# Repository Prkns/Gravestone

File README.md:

💀

6 Key Macropad with USB-C... Still a work in progress.

Feel free to contribute to this project 👍

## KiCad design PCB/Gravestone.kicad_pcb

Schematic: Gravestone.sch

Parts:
C1, C2: 22pF; C_0805_2012Metric_Pad1.15x1.40mm_HandSolder
C3, C4, C5: 0.1uF; C_0805_2012Metric_Pad1.15x1.40mm_HandSolder
C6: 10uF; C_0805_2012Metric_Pad1.15x1.40mm_HandSolder
C7: 1uF; C_0805_2012Metric_Pad1.15x1.40mm_HandSolder
D1: PRTR5V0U2X; SOT-23-6
D2, D3, D4, D5, D6, D7: D_Small; D_SOD-123
F1: 500mA; Fuse_1206_3216Metric
J1: USB_C_Receptacle_USB2.0; USB_C_Receptacle_HRO_TYPE-C-31-M-12
MX1, MX2, MX3, MX4, MX5, MX6: MX-NoLED; MXOnly-1U-NoLED
R1, R7: 10k; R_0805
R2, R3: 5.1k; R_0805
R4, R5: 22; R_0805
SW1: SW_PUSH; SW_SPST_TL3342
U1: ATmega32U2-AU; ATMEGA32U2-AU
Y1: 16MHz; Crystal_SMD_3225-4pin_3.2x2.5mm

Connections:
+5V: C3.1, C4.1, C5.1, C6.1, F1.1, R1.2, U1.4 (VCC), U1.31 (UVCC), U1.32 (AVCC)
COL0: MX1.1, MX4.1, U1.6 (PD0)
COL1: MX2.1, MX5.1, U1.7 (PD1)
COL2: MX3.1, MX6.1, U1.8 (PD2)
D+: D1.6 (IO4), J1.A6, J1.B6, R4.2
D-: D1.1 (IO1), J1.A7, J1.B7, R5.2
GND: C1.2, C2.2, C3.2, C4.2, C5.2, C6.2, C7.2, D1.2 (VN), J1.A1B12, J1.B1A12, J1.S1, R2.1, R3.1, R7.2, SW1.1, U1.3 (GND), U1.28 (UGND), Y1.2, Y1.4
unnamed: C1.1, U1.1 (XTAL1), Y1.1
unnamed: C2.1, U1.2 (PC0/XTAL2), Y1.3
unnamed: C7.1, U1.27 (UCAP)
unnamed: D2.1 (K), MX1.2
unnamed: D3.1 (K), MX2.2
unnamed: D4.1 (K), MX3.2
unnamed: D5.1 (K), MX4.2
unnamed: D6.1 (K), MX5.2
unnamed: D7.1 (K), MX6.2
unnamed: J1.A5, R2.2
unnamed: J1.B5, R3.2
unnamed: R1.1, SW1.2, U1.24 (PC1/~RESET)
unnamed: R4.1, U1.29 (D+)
unnamed: R5.1, U1.30 (D-)
unnamed: R7.1, U1.13 (~HWB~/PD7)
ROW0: D2.2 (A), D3.2 (A), D4.2 (A), U1.9 (PD3)
ROW1: D5.2 (A), D6.2 (A), D7.2 (A)
ROW2: U1.10 (PD4)
VBUS: D1.5 (VP), F1.2, J1.A4B9, J1.B4A9

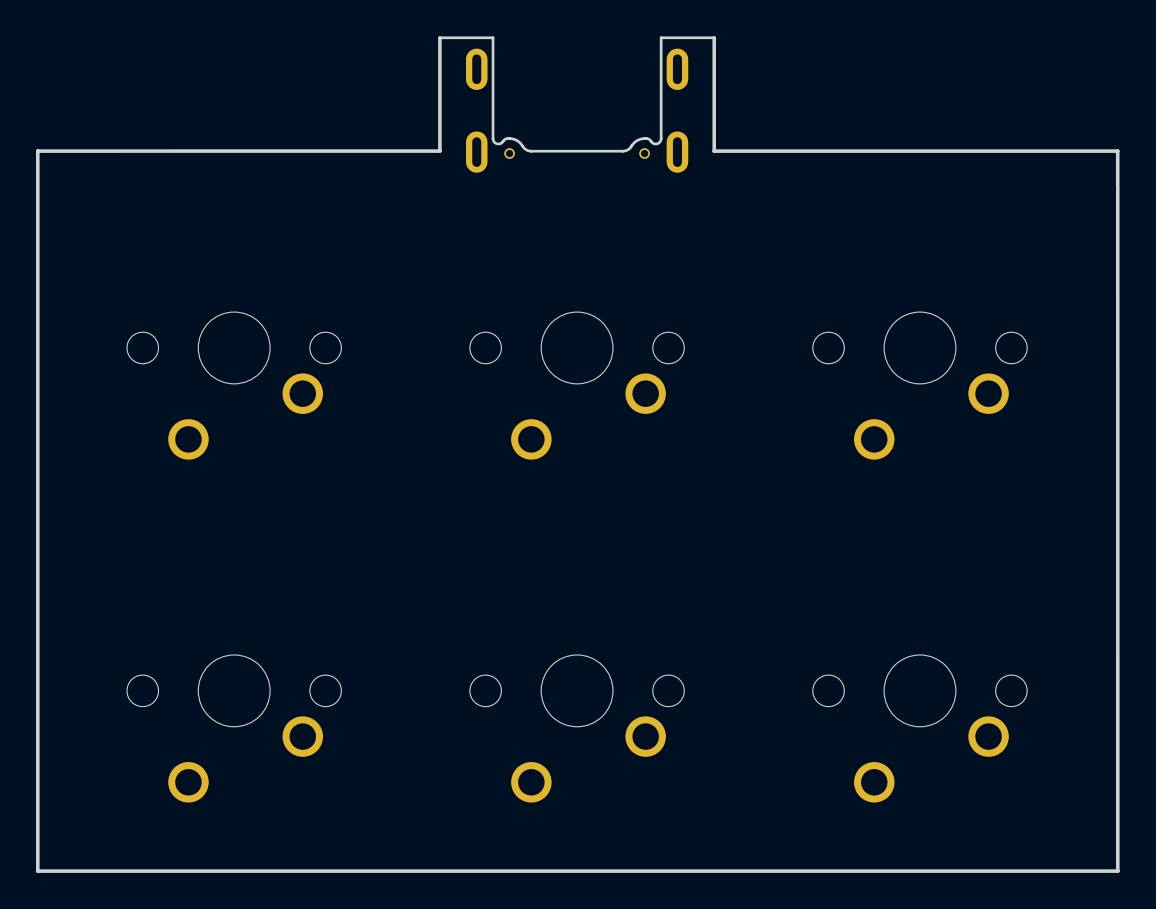
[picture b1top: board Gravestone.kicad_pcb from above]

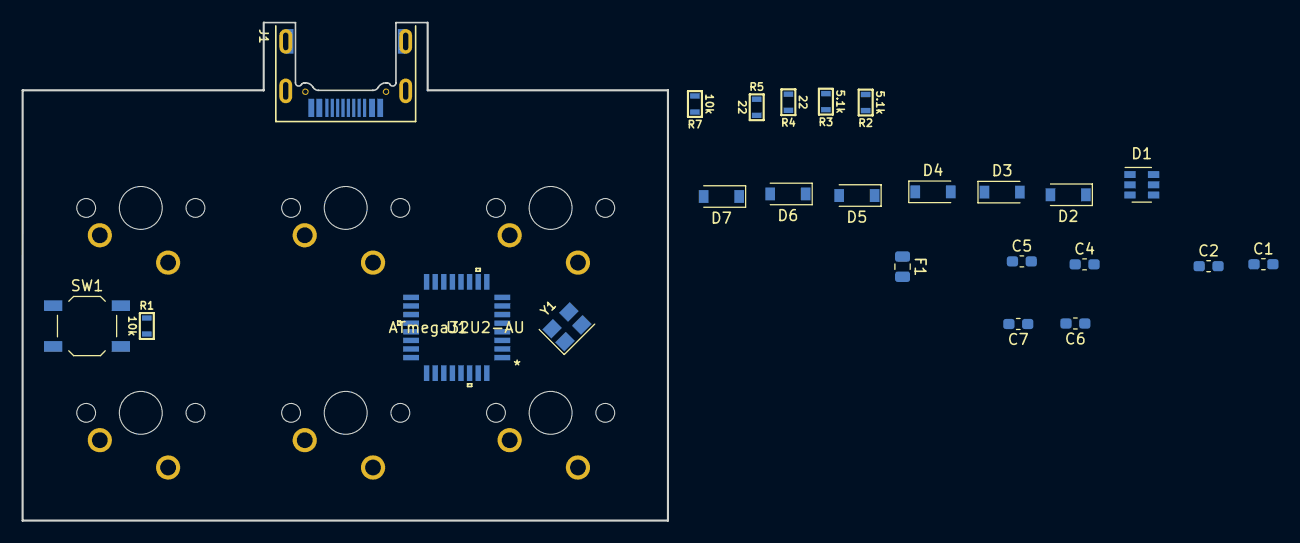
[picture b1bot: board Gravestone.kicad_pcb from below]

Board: 2 copper layers, 60.0 x 46.3 mm, 30 parts (24 on the bottom side), 25 nets, no tracks yet.

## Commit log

2020-08-26 updated ignore
2020-08-26 added renders
2020-08-26 added render models
2020-08-26 added bare case
2020-08-26 added initial PCB
2020-09-06 swapped 32u4 for 32u2 to save space
2020-09-07 9/07
2020-09-07 9/7 usb
2020-09-07 9/07 usb2
2020-09-07 9/7 1021

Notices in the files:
parts and their libraries:
Copyright 2016 Accelerated Designs. All rights reserved.
